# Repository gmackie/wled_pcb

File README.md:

### wLED PCB
This is my first KiCAD project to try and make an esp8266 board to run
[wLED](https://github.com/Aircoookie/WLED)

PCB is being created at
[JLCPCB](https://jlcpcb.com/)

Eventually this will be posted somewhere with more details

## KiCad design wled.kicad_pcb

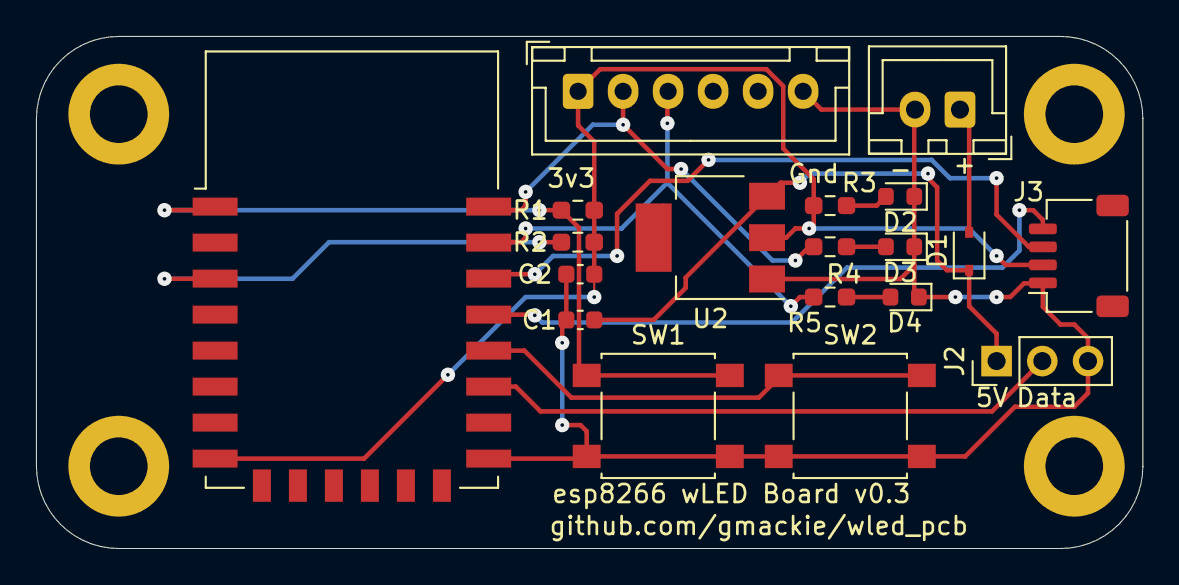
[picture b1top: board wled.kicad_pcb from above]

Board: 2 copper layers, 61.5 x 28.4 mm, 23 parts (0 on the bottom side), 15 nets.

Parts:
C1, C2: 10uF; C_0603_1608Metric
D1: 1N5819; D_SOD-323
D2, D3, D4: LED; LED_0603_1608Metric
H1, H2, H3, H4: MountingHole; MountingHole_3.2mm_M3_DIN965_Pad
J1: PROGRAM_HEADER; JST_XH_B6B-XH-A_1x06_P2.50mm_Vertical
J2: LED0; PinHeader_1x03_P2.54mm_Vertical
J3: QWIIC; JST_SH_SM04B-SRSS-TB_1x04-1MP_P1.00mm_Horizontal
J4: POWER; JST_XH_B2B-XH-A_1x02_P2.50mm_Vertical
R1, R2, R4: 10K; R_0603_1608Metric_Pad0.98x0.95mm_HandSolder
R3, R5: 250; R_0603_1608Metric_Pad0.98x0.95mm_HandSolder
SW1: RESET; SW_SPST_B3S-1000
SW2: FLASH; SW_SPST_B3S-1000
U1: ESP-12F; ESP-12E
U2: AMS1117-3.3; SOT-223-3_TabPin2

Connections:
DATA: J2.2, U1.17
GND: C1.2, C2.2, D2.1, D3.1, D4.1, J1.6, J2.3, J3.1, J4.2, SW1.2, SW2.2, U1.15, U2.1
unnamed: D2.2, R3.2
unnamed: D3.2, R4.2
unnamed: D4.2, R5.1
unnamed: R1.1, SW1.1, U1.1
unnamed: R2.1, U1.3
unnamed: SW2.1, U1.18
RXD: J1.3, R5.2, U1.21
SCL: J3.4, U1.19
SDA: J3.3, U1.20
TXD: J1.2, R4.1, U1.22
VDD3V3: C2.1, J1.1, J3.2, R1.2, R2.2, R3.1, U1.8, U2.2
VDD5V: C1.1, D1.1, J2.1, U2.3
VIN: D1.2, J4.1

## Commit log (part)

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2021-03-27 added readme
2021-03-27 Create LICENSE
2021-03-27 fix vias per JLCPCB email
2021-03-27 add render
2021-03-27 add .gitignore
2021-03-27 Remove ignored files
2021-03-28 update and resubmit
2021-03-30 fix 0603 components
2021-04-02 add correct rotations
2021-05-29 updated parts/placements
2021-05-30 updated pcb origin... still not aligned properly for jlc
2021-06-09 v0.3 (fix LEDs and add reset SW)
2021-06-09 forgot to save schematic
2021-10-18 update schem
